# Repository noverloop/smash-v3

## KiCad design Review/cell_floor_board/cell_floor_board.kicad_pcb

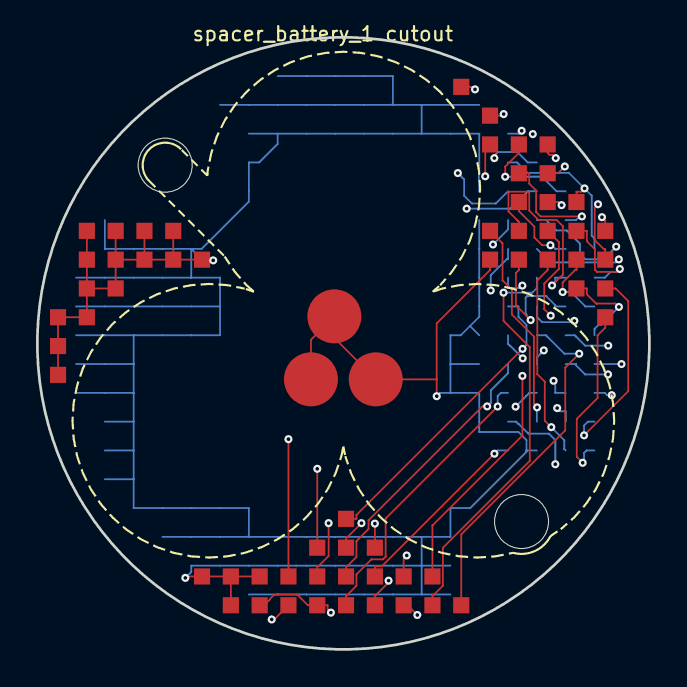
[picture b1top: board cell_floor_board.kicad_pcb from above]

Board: 6 copper layers, 34.0 x 34.0 mm, 7 parts (1 on the bottom side), 35 nets.

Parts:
J_cell_floor_board_spacer_battery_1: LGA_lands; J_cell_floor_board_spacer_battery_1
MECH1, MECH2: smash_mech_potting
P_CELL_TAB_NEG1, P_CELL_TAB_NEG2, P_CELL_TAB_NEG3: CellSolderTab; CellSolderTab_placeholder
P_cell_floor_board_spacer_activation_interface_cell_floor_board: LGA_lands; P_cell_floor_board_spacer_activation_interface_cell_floor_b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

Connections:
3V3: J_cell_floor_board_spacer_battery_1.1, J_cell_floor_board_spacer_battery_1.36, J_cell_floor_board_spacer_battery_1.41, P_cell_floor_board_spacer_activation_in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.1, P_cell_floor_board_spacer_activation_in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.36, P_cell_floor_board_spacer_activation_in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.41
3V3_AON: J_cell_floor_board_spacer_battery_1.2, J_cell_floor_board_spacer_battery_1.37, P_cell_floor_board_spacer_activation_in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.2, P_cell_floor_board_spacer_activation_in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.37
ACTIVATE_CONFIRM: J_cell_floor_board_spacer_battery_1.3, P_cell_floor_board_spacer_activation_in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.3
ACTIVATE_SET: J_cell_floor_board_spacer_battery_1.4, P_cell_floor_board_spacer_activation_in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.4
BAT_PROT: J_cell_floor_board_spacer_battery_1.5, J_cell_floor_board_spacer_battery_1.38, P_cell_floor_board_spacer_activation_in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.5, P_cell_floor_board_spacer_activation_in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.38
BAT_RAW: J_cell_floor_board_spacer_battery_1.6, J_cell_floor_board_spacer_battery_1.39, P_cell_floor_board_spacer_activation_in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.6, P_cell_floor_board_spacer_activation_in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.39
BOOT0: J_cell_floor_board_spacer_battery_1.7, P_cell_floor_board_spacer_activation_in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.7
COMP_5V: J_cell_floor_board_spacer_battery_1.8, J_cell_floor_board_spacer_battery_1.40, P_cell_floor_board_spacer_activation_in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.8, P_cell_floor_board_spacer_activation_in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.40
COMP_SWDCLK: J_cell_floor_board_spacer_battery_1.9, P_cell_floor_board_spacer_activation_in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.9
COMP_SWDIO: J_cell_floor_board_spacer_battery_1.10, P_cell_floor_board_spacer_activation_in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.10
EXT_CAN_RX: J_cell_floor_board_spacer_battery_1.11, P_cell_floor_board_spacer_activation_in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.11
EXT_CAN_TX: J_cell_floor_board_spacer_battery_1.12, P_cell_floor_board_spacer_activation_in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.12
FIN1_AOUT1: J_cell_floor_board_spacer_battery_1.13, P_cell_floor_board_spacer_activation_in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.13
FIN2_AOUT1: J_cell_floor_board_spacer_battery_1.14, P_cell_floor_board_spacer_activation_in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.14
FIN3_AOUT1: J_cell_floor_board_spacer_battery_1.15, P_cell_floor_board_spacer_activation_in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.15
FIN4_AOUT1: J_cell_floor_board_spacer_battery_1.16, P_cell_floor_board_spacer_activation_in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.16
FIN_HALL: J_cell_floor_board_spacer_battery_1.17, P_cell_floor_board_spacer_activation_in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.17
FIN_VREF: J_cell_floor_board_spacer_battery_1.18, P_cell_floor_board_spacer_activation_in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.18
FLEX_GND: J_cell_floor_board_spacer_battery_1.19, J_cell_floor_board_spacer_battery_1.42, J_cell_floor_board_spacer_battery_1.43, J_cell_floor_board_spacer_battery_1.44, J_cell_floor_board_spacer_battery_1.45, J_cell_floor_board_spacer_battery_1.46, J_cell_floor_board_spacer_battery_1.47, J_cell_floor_board_spacer_battery_1.48, J_cell_floor_board_spacer_battery_1.49, J_cell_floor_board_spacer_battery_1.50, J_cell_floor_board_spacer_battery_1.51, J_cell_floor_board_spacer_battery_1.52, J_cell_floor_board_spacer_battery_1.53, J_cell_floor_board_spacer_battery_1.54, J_cell_floor_board_spacer_battery_1.55, J_cell_floor_board_spacer_battery_1.56, J_cell_floor_board_spacer_battery_1.57, J_cell_floor_board_spacer_battery_1.58, J_cell_floor_board_spacer_battery_1.59, J_cell_floor_board_spacer_battery_1.60, P_CELL_TAB_NEG1.1, P_CELL_TAB_NEG2.1, P_CELL_TAB_NEG3.1, P_cell_floor_board_spacer_activation_in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.19, P_cell_floor_board_spacer_activation_in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.42, P_cell_floor_board_spacer_activation_in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.43, P_cell_floor_board_spacer_activation_in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.44, P_cell_floor_board_spacer_activation_in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.45, P_cell_floor_board_spacer_activation_in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.46, P_cell_floor_board_spacer_activation_in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.47, P_cell_floor_board_spacer_activation_in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.48, P_cell_floor_board_spacer_activation_in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.49, P_cell_floor_board_spacer_activation_in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.50, P_cell_floor_board_spacer_activation_in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.51, P_cell_floor_board_spacer_activation_in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.52, P_cell_floor_board_spacer_activation_in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.53, P_cell_floor_board_spacer_activation_in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.54, P_cell_floor_board_spacer_activation_in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.55, P_cell_floor_board_spacer_activation_in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.56, P_cell_floor_board_spacer_activation_in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.57, P_cell_floor_board_spacer_activation_in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.58, P_cell_floor_board_spacer_activation_in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.59, P_cell_floor_board_spacer_activation_in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.60, P_cell_floor_board_spacer_activation_in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.61, P_cell_floor_board_spacer_activation_in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.62, P_cell_floor_board_spacer_activation_in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.63, P_cell_floor_board_spacer_activation_in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.64, P_cell_floor_board_spacer_activation_in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.65, P_cell_floor_board_spacer_activation_in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.66, P_cell_floor_board_spacer_activation_in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.67, P_cell_floor_board_spacer_activation_in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.68, P_cell_floor_board_spacer_activation_in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.69, P_cell_floor_board_spacer_activation_in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.70, P_cell_floor_board_spacer_activation_in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.71, P_cell_floor_board_spacer_activation_in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.72, P_cell_floor_board_spacer_activation_in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.73, P_cell_floor_board_spacer_activation_in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.74, P_cell_floor_board_spacer_activation_in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.75, P_cell_floor_board_spacer_activation_in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.76, P_cell_floor_board_spacer_activation_in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.77, P_cell_floor_board_spacer_activation_in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.78, P_cell_floor_board_spacer_activation_in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.79, P_cell_floor_board_spacer_activation_in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.80, P_cell_floor_board_spacer_activation_in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.81, P_cell_floor_board_spacer_activation_in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.82, P_cell_floor_board_spacer_activation_in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.83, P_cell_floor_board_spacer_activation_in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.84, P_cell_floor_board_spacer_activation_in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.85, P_cell_floor_board_spacer_activation_in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.86, P_cell_floor_board_spacer_activation_in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.87, P_cell_floor_board_spacer_activation_in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.88, P_cell_floor_board_spacer_activation_in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.89, P_cell_floor_board_spacer_activation_in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.90, P_cell_floor_board_spacer_activation_in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.91, P_cell_floor_board_spacer_activation_in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.92, P_cell_floor_board_spacer_activation_in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.93, P_cell_floor_board_spacer_activation_in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.94, P_cell_floor_board_spacer_activation_in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.95, P_cell_floor_board_spacer_activation_in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.96, P_cell_floor_board_spacer_activation_in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.97, P_cell_floor_board_spacer_activation_in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.98, P_cell_floor_board_spacer_activation_in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.99, P_cell_floor_board_spacer_activation_in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.100, P_cell_floor_board_spacer_activation_in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.101, P_cell_floor_board_spacer_activation_in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.102, P_cell_floor_board_spacer_activation_in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.103, P_cell_floor_board_spacer_activation_in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.104, P_cell_floor_board_spacer_activation_in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.105, P_cell_floor_board_spacer_activation_in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.106, P_cell_floor_board_spacer_activation_in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.107, P_cell_floor_board_spacer_activation_in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.108, P_cell_floor_board_spacer_activation_in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.109, P_cell_floor_board_spacer_activation_in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.110, P_cell_floor_board_spacer_activation_in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.111, P_cell_floor_board_spacer_activation_in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.112, P_cell_floor_board_spacer_activation_in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.113, P_cell_floor_board_spacer_activation_in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.114, P_cell_floor_board_spacer_activation_in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.115, P_cell_floor_board_spacer_activation_in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.116, P_cell_floor_board_spacer_activation_in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.117, P_cell_floor_board_spacer_activation_in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.118, P_cell_floor_board_spacer_activation_in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.119, P_cell_floor_board_spacer_activation_in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.120, P_cell_floor_board_spacer_activation_in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.121, P_cell_floor_board_spacer_activation_in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.122, P_cell_floor_board_spacer_activation_in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.123, P_cell_floor_board_spacer_activation_in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.124, P_cell_floor_board_spacer_activation_in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.125, P_cell_floor_board_spacer_activation_in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.126, P_cell_floor_board_spacer_activation_in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.127, P_cell_floor_board_spacer_activation_in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.128, P_cell_floor_board_spacer_activation_in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.129, P_cell_floor_board_spacer_activation_in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.130, P_cell_floor_board_spacer_activation_in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.131, P_cell_floor_board_spacer_activation_in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.132, P_cell_floor_board_spacer_activation_in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.133, P_cell_floor_board_spacer_activation_in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.134, P_cell_floor_board_spacer_activation_in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.135, P_cell_floor_board_spacer_activation_in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.136, P_cell_floor_board_spacer_activation_in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.137, P_cell_floor_board_spacer_activation_in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.138, P_cell_floor_board_spacer_activation_in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.139, P_cell_floor_board_spacer_activation_in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.140, P_cell_floor_board_spacer_activation_in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.141, P_cell_floor_board_spacer_activation_in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.142, P_cell_floor_board_spacer_activation_in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.143, P_cell_floor_board_spacer_activation_in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.144, P_cell_floor_board_spacer_activation_in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.145, P_cell_floor_board_spacer_activation_in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.146, P_cell_floor_board_spacer_activation_in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.147, P_cell_floor_board_spacer_activation_in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.148, P_cell_floor_board_spacer_activation_in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.149, P_cell_floor_board_spacer_activation_in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.150
GPIO_EXT_0: J_cell_floor_board_spacer_battery_1.20, P_cell_floor_board_spacer_activation_in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.20
GPIO_EXT_1: J_cell_floor_board_spacer_battery_1.21, P_cell_floor_board_spacer_activation_in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.21
GPIO_EXT_2: J_cell_floor_board_spacer_battery_1.22, P_cell_floor_board_spacer_activation_in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.22
GPIO_EXT_3: J_cell_floor_board_spacer_battery_1.23, P_cell_floor_board_spacer_activation_in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.23
H3LIS_INT1: J_cell_floor_board_spacer_battery_1.24, P_cell_floor_board_spacer_activation_in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.24
I2C3_SCL: J_cell_floor_board_spacer_battery_1.25, P_cell_floor_board_spacer_activation_in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.25
I2C3_SDA: J_cell_floor_board_spacer_battery_1.26, P_cell_floor_board_spacer_activation_in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.26
JUMP_WAKE: J_cell_floor_board_spacer_battery_1.27, P_cell_floor_board_spacer_activation_in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.27
NRST: J_cell_floor_board_spacer_battery_1.28, P_cell_floor_board_spacer_activation_in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.28
SWO: J_cell_floor_board_spacer_battery_1.29, P_cell_floor_board_spacer_activation_in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.29
SYS_I2C_SCL: J_cell_floor_board_spacer_battery_1.30, P_cell_floor_board_spacer_activation_in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.30
SYS_I2C_SDA: J_cell_floor_board_spacer_battery_1.31, P_cell_floor_board_spacer_activation_in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.31
SYS_SPI_CS_FIN: J_cell_floor_board_spacer_battery_1.32, P_cell_floor_board_spacer_activation_in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.32
SYS_SPI_MISO: J_cell_floor_board_spacer_battery_1.33, P_cell_floor_board_spacer_activation_in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.33
SYS_SPI_MOSI: J_cell_floor_board_spacer_battery_1.34, P_cell_floor_board_spacer_activation_in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.34
SYS_SPI_SCLK: J_cell_floor_board_spacer_battery_1.35, P_cell_floor_board_spacer_activation_in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.35

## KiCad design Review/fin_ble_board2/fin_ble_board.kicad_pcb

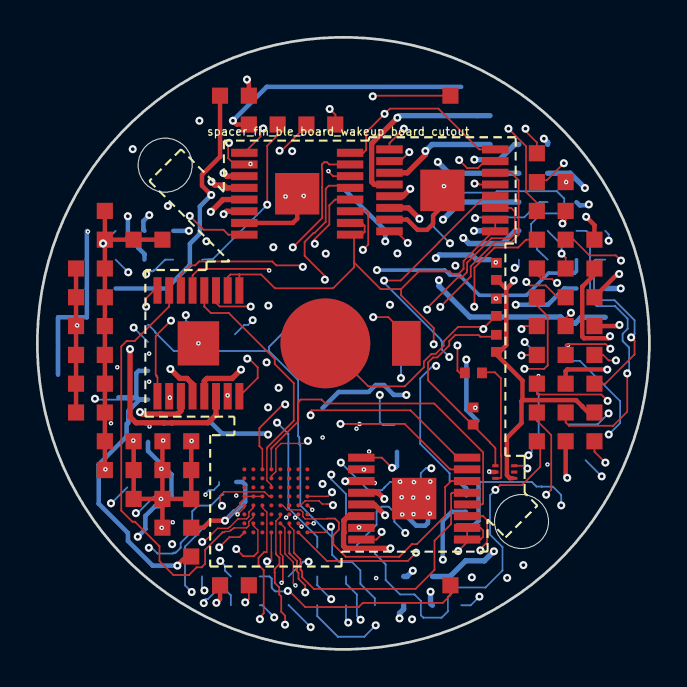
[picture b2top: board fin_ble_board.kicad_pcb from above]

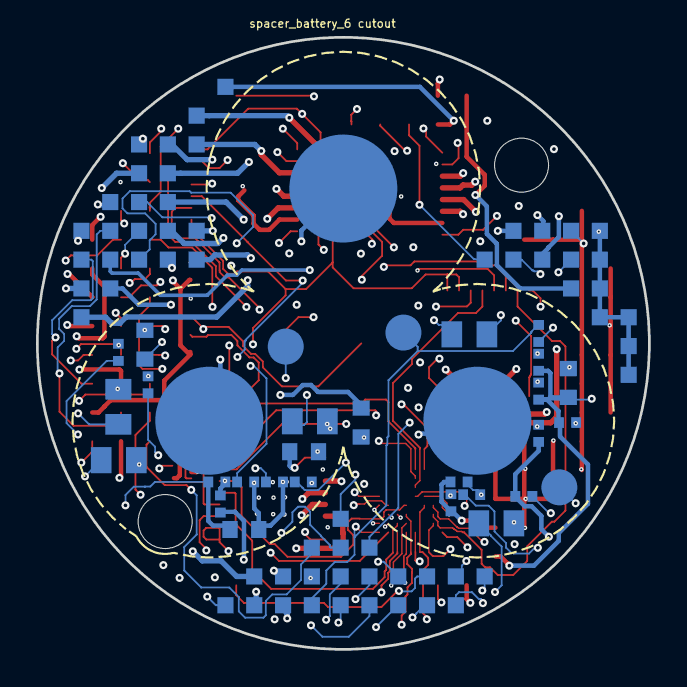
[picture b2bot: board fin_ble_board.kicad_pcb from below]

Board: 14 copper layers, 34.0 x 34.0 mm, 44 parts (31 on the bottom side), 81 nets.

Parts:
C_COMP_PZ: C0402 X7R 100nF; Capacitor_SMD_C_0402_1005Metric
C_FIN1_DVDD, C_FIN2_DVDD, C_FIN3_DVDD, C_FIN4_DVDD: C-Series MIL-PRF-32535 X7R 0805 1uF; Capacitor_SMD_C_0805_2012Metric
C_FIN1_VM, C_FIN2_VM, C_FIN3_VM, C_FIN4_VM: C0402 X7R 100nF; Capacitor_SMD_C_0402_1005Metric
C_FIN_VM_BULK_1, C_FIN_VM_BULK_2, C_FIN_VM_BULK_3, C_FIN_VM_BULK_4, C_FIN_VM_BULK_5: C-Series MIL-PRF-32535 X7R 0603 2.2uF; Capacitor_SMD_C_0603_1608Metric
C_FIN_VREF: C0402 X7R 100nF; Capacitor_SMD_C_0402_1005Metric
C_G0B1_FIN_BULK: C-Series MIL-PRF-32535 X7R 0805 1uF; Capacitor_SMD_C_0805_2012Metric
C_G0B1_FIN_NRST, C_G0B1_FIN_VDD1, C_G0B1_FIN_VDD2, C_G0B1_FIN_VREF: C0402 X7R 100nF; Capacitor_SMD_C_0402_1005Metric
C_J_HALL_FIN_VCC: C0402 X7R 100nF; Capacitor_SMD_C_0402_1005Metric
J_HALL_FIN_GND: J_HALL_FIN_GND; Pogo_Pad_D2.0mm
J_HALL_FIN_OUT: J_HALL_FIN_OUT; Pogo_Pad_D2.0mm
J_HALL_FIN_VCC: J_HALL_FIN_VCC; Pogo_Pad_D2.0mm
J_fin_ble_board_spacer_fin_ble_board_wakeup_board: LGA_lands; J_fin_ble_board_spacer_fin_ble_board_wakeup_board
P_CELL_CONTACTS: BatteryContacts_3
P_PIEZO: SMD10T04R111; PiezoDisc_SMD10T04R111
P_fin_ble_board_spacer_battery_6: LGA_lands; P_fin_ble_board_spacer_battery_6
R_COMP_SER: CRCW0402 100k 1% e3; Resistor_SMD_R_0402_1005Metric
R_FIN1_DECAY, R_FIN2_DECAY, R_FIN3_DECAY, R_FIN4_DECAY: CRCW0402 44.2k 1% e3; Resistor_SMD_R_0402_1005Metric
R_G0B1_FIN_NRST: CRCW0402 10k 1% e3; Resistor_SMD_R_0402_1005Metric
R_J_HALL_FIN_PU: CRCW0402 10k 1% e3; Resistor_SMD_R_0402_1005Metric
R_PIEZO_BLEED: CRCW0402 1M 1% e3; Resistor_SMD_R_0402_1005Metric
R_THR1: CRCW0402 1M 1% e3; Resistor_SMD_R_0402_1005Metric
R_THR2: CRCW0402 100k 1% e3; Resistor_SMD_R_0402_1005Metric
U_COMP_PZ: TLV3691IDPFR; DPF0006A
U_FIN1, U_FIN2, U_FIN3, U_FIN4: DRV8428EPWPR; SOP65P640X120-17N
U_G0B1_FIN: STM32G0B1REI6N; BGA64C50P8X8_500X500X60

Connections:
3V3: C_G0B1_FIN_BULK.1, C_G0B1_FIN_VDD1.1, C_G0B1_FIN_VDD2.1, C_G0B1_FIN_VREF.1, C_J_HALL_FIN_VCC.1, J_HALL_FIN_VCC.1, J_fin_ble_board_spacer_fin_ble_board_wa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.1, J_fin_ble_board_spacer_fin_ble_board_wa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.35, J_fin_ble_board_spacer_fin_ble_board_wa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.41, P_fin_ble_board_spacer_battery_6.23, P_fin_ble_board_spacer_battery_6.47, P_fin_ble_board_spacer_battery_6.52, R_G0B1_FIN_NRST.1, R_J_HALL_FIN_PU.1, U_G0B1_FIN.D1, U_G0B1_FIN.D2, U_G0B1_FIN.D3, U_G0B1_FIN.D8
3V3_AON: C_COMP_PZ.1, J_fin_ble_board_spacer_fin_ble_board_wa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.2, J_fin_ble_board_spacer_fin_ble_board_wa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.36, P_fin_ble_board_spacer_battery_6.24, P_fin_ble_board_spacer_battery_6.48, R_THR1.1, U_COMP_PZ.6
ACTIVATE_CONFIRM: J_fin_ble_board_spacer_fin_ble_board_wa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.3, P_fin_ble_board_spacer_battery_6.3
ACTIVATE_SET: J_fin_ble_board_spacer_fin_ble_board_wa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.4, P_fin_ble_board_spacer_battery_6.4
BAT_CELL1_POS: J_fin_ble_board_spacer_fin_ble_board_wa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.5, P_CELL_CONTACTS.1
BAT_CELL2_POS: J_fin_ble_board_spacer_fin_ble_board_wa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.6, P_CELL_CONTACTS.2
BAT_CELL3_POS: J_fin_ble_board_spacer_fin_ble_board_wa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.7, P_CELL_CONTACTS.3
BAT_PROT: J_fin_ble_board_spacer_fin_ble_board_wa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.8, J_fin_ble_board_spacer_fin_ble_board_wa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.37, P_fin_ble_board_spacer_battery_6.5, P_fin_ble_board_spacer_battery_6.49
BAT_RAW: J_fin_ble_board_spacer_fin_ble_board_wa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.9, J_fin_ble_board_spacer_fin_ble_board_wa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.38, P_fin_ble_board_spacer_battery_6.6, P_fin_ble_board_spacer_battery_6.50
BOOT0: J_fin_ble_board_spacer_fin_ble_board_wa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.10, P_fin_ble_board_spacer_battery_6.7
COMP_5V: J_fin_ble_board_spacer_fin_ble_board_wa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.11, J_fin_ble_board_spacer_fin_ble_board_wa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.39, P_fin_ble_board_spacer_battery_6.8, P_fin_ble_board_spacer_battery_6.51
COMP_5V_RAW: C_FIN1_VM.1, C_FIN2_VM.1, C_FIN3_VM.1, C_FIN4_VM.1, C_FIN_VM_BULK_1.1, C_FIN_VM_BULK_2.1, C_FIN_VM_BULK_3.1, C_FIN_VM_BULK_4.1, C_FIN_VM_BULK_5.1, J_fin_ble_board_spacer_fin_ble_board_wa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.12, J_fin_ble_board_spacer_fin_ble_board_wa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.40, U_FIN1.1, U_FIN2.1, U_FIN3.1, U_FIN4.1
COMP_INM: R_THR1.2, R_THR2.1, U_COMP_PZ.3
COMP_INP: R_COMP_SER.2, U_COMP_PZ.1
COMP_OUT: J_fin_ble_board_spacer_fin_ble_board_wa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.13, U_COMP_PZ.4
COMP_SWDCLK: J_fin_ble_board_spacer_fin_ble_board_wa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.14, P_fin_ble_board_spacer_battery_6.9
COMP_SWDIO: J_fin_ble_board_spacer_fin_ble_board_wa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.15, P_fin_ble_board_spacer_battery_6.10
EXT_CAN_RX: J_fin_ble_board_spacer_fin_ble_board_wa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.16, P_fin_ble_board_spacer_battery_6.11
EXT_CAN_TX: J_fin_ble_board_spacer_fin_ble_board_wa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.17, P_fin_ble_board_spacer_battery_6.14
FIN1_AEN: U_FIN1.15, U_G0B1_FIN.E3
FIN1_AOUT1: P_fin_ble_board_spacer_battery_6.13, U_FIN1.3
FIN1_AOUT2: P_fin_ble_board_spacer_battery_6.12, U_FIN1.4
FIN1_APH: U_FIN1.14, U_G0B1_FIN.H5
FIN1_BEN: U_FIN1.13, U_G0B1_FIN.F5
FIN1_BOUT1: P_fin_ble_board_spacer_battery_6.15, U_FIN1.6
FIN1_BOUT2: P_fin_ble_board_spacer_battery_6.16, U_FIN1.5
FIN1_BPH: U_FIN1.12, U_G0B1_FIN.B4
FIN1_DECAY: R_FIN1_DECAY.1, U_FIN1.11
FIN1_DVDD: C_FIN1_DVDD.1, U_FIN1.8
FIN2_AEN: U_FIN2.15, U_G0B1_FIN.F2
FIN2_AOUT1: P_fin_ble_board_spacer_battery_6.17, U_FIN2.3
FIN2_AOUT2: P_fin_ble_board_spacer_battery_6.18, U_FIN2.4
FIN2_APH: U_FIN2.14, U_G0B1_FIN.H6
FIN2_BEN: U_FIN2.13, U_G0B1_FIN.G5
FIN2_BOUT1: P_fin_ble_board_spacer_battery_6.19, U_FIN2.6
FIN2_BOUT2: P_fin_ble_board_spacer_battery_6.20, U_FIN2.5
FIN2_BPH: U_FIN2.12, U_G0B1_FIN.C4
FIN2_DECAY: R_FIN2_DECAY.1, U_FIN2.11
FIN2_DVDD: C_FIN2_DVDD.1, U_FIN2.8
FIN3_AEN: U_FIN3.15, U_G0B1_FIN.G2
FIN3_AOUT1: P_fin_ble_board_spacer_battery_6.21, U_FIN3.3
FIN3_AOUT2: P_fin_ble_board_spacer_battery_6.22, U_FIN3.4
FIN3_APH: U_FIN3.14, U_G0B1_FIN.E7
FIN3_BEN: U_FIN3.13, U_G0B1_FIN.H7
FIN3_BOUT1: P_fin_ble_board_spacer_battery_6.1, U_FIN3.6
FIN3_BOUT2: P_fin_ble_board_spacer_battery_6.2, U_FIN3.5
FIN3_BPH: U_FIN3.12, U_G0B1_FIN.D4
FIN3_DECAY: R_FIN3_DECAY.1, U_FIN3.11
FIN3_DVDD: C_FIN3_DVDD.1, U_FIN3.8
FIN4_AEN: U_FIN4.15, U_G0B1_FIN.H1
FIN4_AOUT1: P_fin_ble_board_spacer_battery_6.25, U_FIN4.3
FIN4_AOUT2: P_fin_ble_board_spacer_battery_6.26, U_FIN4.4
FIN4_APH: U_FIN4.14, U_G0B1_FIN.E5
FIN4_BEN: U_FIN4.13, U_G0B1_FIN.G6
FIN4_BOUT1: P_fin_ble_board_spacer_battery_6.27, U_FIN4.6
FIN4_BOUT2: P_fin_ble_board_spacer_battery_6.28, U_FIN4.5
FIN4_BPH: U_FIN4.12, U_G0B1_FIN.A4
FIN4_DECAY: R_FIN4_DECAY.1, U_FIN4.11
FIN4_DVDD: C_FIN4_DVDD.1, U_FIN4.8
FIN_HALL: J_HALL_FIN_OUT.1, P_fin_ble_board_spacer_battery_6.29, R_J_HALL_FIN_PU.2, U_G0B1_FIN.H8
FIN_NSLEEP: U_FIN1.16, U_FIN2.16, U_FIN3.16, U_FIN4.16, U_G0B1_FIN.A3
FIN_VREF: C_FIN_VREF.1, U_FIN1.9, U_FIN1.10, U_FIN2.9, U_FIN2.10, U_FIN3.9, U_FIN3.10, U_FIN4.9, U_FIN4.10, U_G0B1_FIN.H4
FLEX_GND: C_COMP_PZ.2, C_FIN1_DVDD.2, C_FIN1_VM.2, C_FIN2_DVDD.2, C_FIN2_VM.2, C_FIN3_DVDD.2, C_FIN3_VM.2, C_FIN4_DVDD.2, C_FIN4_VM.2, C_FIN_VM_BULK_1.2, C_FIN_VM_BULK_2.2, C_FIN_VM_BULK_3.2, C_FIN_VM_BULK_4.2, C_FIN_VM_BULK_5.2, C_FIN_VREF.2, C_G0B1_FIN_BULK.2, C_G0B1_FIN_NRST.2, C_G0B1_FIN_VDD1.2, C_G0B1_FIN_VDD2.2, C_G0B1_FIN_VREF.2, C_J_HALL_FIN_VCC.2, J_HALL_FIN_GND.1, J_fin_ble_board_spacer_fin_ble_board_wa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.18, J_fin_ble_board_spacer_fin_ble_board_wa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.42, J_fin_ble_board_spacer_fin_ble_board_wa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.43, J_fin_ble_board_spacer_fin_ble_board_wa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.44, J_fin_ble_board_spacer_fin_ble_board_wa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.45, J_fin_ble_board_spacer_fin_ble_board_wa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.46, J_fin_ble_board_spacer_fin_ble_board_wa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.47, J_fin_ble_board_spacer_fin_ble_board_wa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.48, J_fin_ble_board_spacer_fin_ble_board_wa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.49, J_fin_ble_board_spacer_fin_ble_board_wa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.50, J_fin_ble_board_spacer_fin_ble_board_wa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.51, J_fin_ble_board_spacer_fin_ble_board_wa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.52, J_fin_ble_board_spacer_fin_ble_board_wa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.53, J_fin_ble_board_spacer_fin_ble_board_wa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.54, J_fin_ble_board_spacer_fin_ble_board_wa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.55, J_fin_ble_board_spacer_fin_ble_board_wa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.56, J_fin_ble_board_spacer_fin_ble_board_wa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.57, J_fin_ble_board_spacer_fin_ble_board_wa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.58, J_fin_ble_board_spacer_fin_ble_board_wa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.59, J_fin_ble_board_spacer_fin_ble_board_wa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.60, J_fin_ble_board_spacer_fin_ble_board_wa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.61, J_fin_ble_board_spacer_fin_ble_board_wa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.62, J_fin_ble_board_spacer_fin_ble_board_wa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.63, J_fin_ble_board_spacer_fin_ble_board_wa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.64, J_fin_ble_board_spacer_fin_ble_board_wa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.65, J_fin_ble_board_spacer_fin_ble_board_wa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.66, J_fin_ble_board_spacer_fin_ble_board_wa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.67, J_fin_ble_board_spacer_fin_ble_board_wa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.68, J_fin_ble_board_spacer_fin_ble_board_wa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.69, P_PIEZO.2, P_fin_ble_board_spacer_battery_6.30, P_fin_ble_board_spacer_battery_6.53, P_fin_ble_board_spacer_battery_6.54, P_fin_ble_board_spacer_battery_6.55, P_fin_ble_board_spacer_battery_6.56, P_fin_ble_board_spacer_battery_6.57, P_fin_ble_board_spacer_battery_6.58, P_fin_ble_board_spacer_battery_6.59, P_fin_ble_board_spacer_battery_6.60, R_FIN1_DECAY.2, R_FIN2_DECAY.2, R_FIN3_DECAY.2, R_FIN4_DECAY.2, R_PIEZO_BLEED.2, R_THR2.2, U_COMP_PZ.2, U_FIN1.2, U_FIN1.7, U_FIN1.17, U_FIN2.2, U_FIN2.7, U_FIN2.17, U_FIN3.2, U_FIN3.7, U_FIN3.17, U_FIN4.2, U_FIN4.7, U_FIN4.17, U_G0B1_FIN.E1, U_G0B1_FIN.E8
G0B1_FIN_NRST: C_G0B1_FIN_NRST.1, R_G0B1_FIN_NRST.2, U_G0B1_FIN.E2
GPIO_EXT_0: J_fin_ble_board_spacer_fin_ble_board_wa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.19, P_fin_ble_board_spacer_battery_6.31
GPIO_EXT_1: J_fin_ble_board_spacer_fin_ble_board_wa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.20, P_fin_ble_board_spacer_battery_6.32
GPIO_EXT_2: J_fin_ble_board_spacer_fin_ble_board_wa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.21, P_fin_ble_board_spacer_battery_6.33
GPIO_EXT_3: J_fin_ble_board_spacer_fin_ble_board_wa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.22, P_fin_ble_board_spacer_battery_6.34
H3LIS_INT1: J_fin_ble_board_spacer_fin_ble_board_wa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.23, P_fin_ble_board_spacer_battery_6.35
I2C3_SCL: J_fin_ble_board_spacer_fin_ble_board_wa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.24, P_fin_ble_board_spacer_battery_6.36
I2C3_SDA: J_fin_ble_board_spacer_fin_ble_board_wa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.25, P_fin_ble_board_spacer_battery_6.37
JUMP_WAKE: J_fin_ble_board_spacer_fin_ble_board_wa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.26, P_fin_ble_board_spacer_battery_6.38
NRST: J_fin_ble_board_spacer_fin_ble_board_wa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.27, P_fin_ble_board_spacer_battery_6.39
PIEZO_P: P_PIEZO.1, R_COMP_SER.1, R_PIEZO_BLEED.1
SWO: J_fin_ble_board_spacer_fin_ble_board_wa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.28, P_fin_ble_board_spacer_battery_6.40
SYS_I2C_SCL: J_fin_ble_board_spacer_fin_ble_board_wa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.29, P_fin_ble_board_spacer_battery_6.41
SYS_I2C_SDA: J_fin_ble_board_spacer_fin_ble_board_wa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.30, P_fin_ble_board_spacer_battery_6.42
SYS_SPI_CS_FIN: J_fin_ble_board_spacer_fin_ble_board_wa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.31, P_fin_ble_board_spacer_battery_6.43, U_G0B1_FIN.G7
SYS_SPI_MISO: J_fin_ble_board_spacer_fin_ble_board_wa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.32, P_fin_ble_board_spacer_battery_6.44, U_G0B1_FIN.F6
SYS_SPI_MOSI: J_fin_ble_board_spacer_fin_ble_board_wa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.33, P_fin_ble_board_spacer_battery_6.45, U_G0B1_FIN.F7
SYS_SPI_SCLK: J_fin_ble_board_spacer_fin_ble_board_wa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.34, P_fin_ble_board_spacer_battery_6.46, U_G0B1_FIN.G8

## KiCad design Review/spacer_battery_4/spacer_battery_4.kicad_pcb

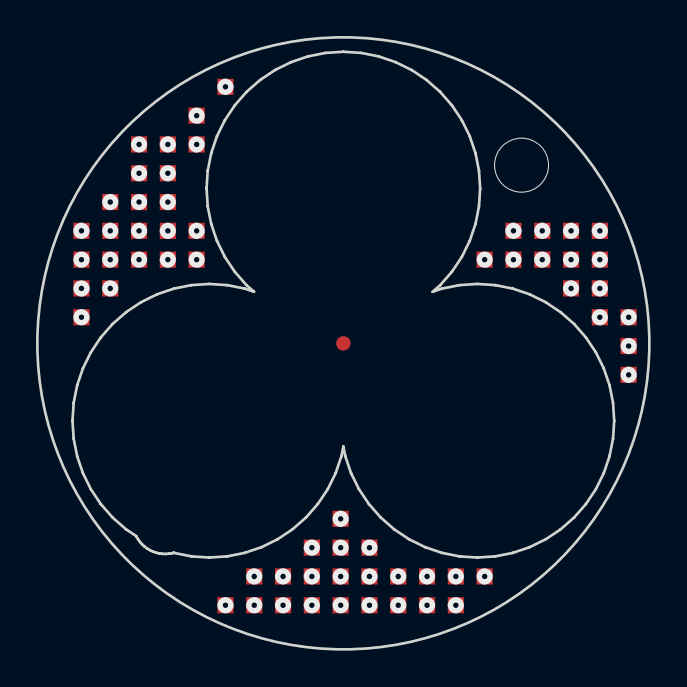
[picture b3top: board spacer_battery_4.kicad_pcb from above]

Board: 2 copper layers, 34.0 x 34.0 mm, 3 parts (1 on the bottom side), 35 nets, no tracks yet.

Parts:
J_spacer_battery_4_top: LGA_lands; J_spacer_battery_4_top
P_spacer_battery_4_bot: LGA_lands; P_spacer_battery_4_bot
SP_battery_4: SP_battery_4; Spacer_Mechanical_34mm

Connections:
3V3: J_spacer_battery_4_top.1, J_spacer_battery_4_top.36, J_spacer_battery_4_top.41, P_spacer_battery_4_bot.1, P_spacer_battery_4_bot.36, P_spacer_battery_4_bot.41
3V3_AON: J_spacer_battery_4_top.2, J_spacer_battery_4_top.37, P_spacer_battery_4_bot.2, P_spacer_battery_4_bot.37
ACTIVATE_CONFIRM: J_spacer_battery_4_top.3, P_spacer_battery_4_bot.3
ACTIVATE_SET: J_spacer_battery_4_top.4, P_spacer_battery_4_bot.4
BAT_PROT: J_spacer_battery_4_top.5, J_spacer_battery_4_top.38, P_spacer_battery_4_bot.5, P_spacer_battery_4_bot.38
BAT_RAW: J_spacer_battery_4_top.6, J_spacer_battery_4_top.39, P_spacer_battery_4_bot.6, P_spacer_battery_4_bot.39
BOOT0: J_spacer_battery_4_top.7, P_spacer_battery_4_bot.7
COMP_5V: J_spacer_battery_4_top.8, J_spacer_battery_4_top.40, P_spacer_battery_4_bot.8, P_spacer_battery_4_bot.40
COMP_SWDCLK: J_spacer_battery_4_top.9, P_spacer_battery_4_bot.9
COMP_SWDIO: J_spacer_battery_4_top.10, P_spacer_battery_4_bot.10
EXT_CAN_RX: J_spacer_battery_4_top.11, P_spacer_battery_4_bot.11
EXT_CAN_TX: J_spacer_battery_4_top.12, P_spacer_battery_4_bot.12
FIN1_AOUT1: J_spacer_battery_4_top.13, P_spacer_battery_4_bot.13
FIN2_AOUT1: J_spacer_battery_4_top.14, P_spacer_battery_4_bot.14
FIN3_AOUT1: J_spacer_battery_4_top.15, P_spacer_battery_4_bot.15
FIN4_AOUT1: J_spacer_battery_4_top.16, P_spacer_battery_4_bot.16
FIN_HALL: J_spacer_battery_4_top.17, P_spacer_battery_4_bot.17
FIN_VREF: J_spacer_battery_4_top.18, P_spacer_battery_4_bot.18
FLEX_GND: J_spacer_battery_4_top.19, J_spacer_battery_4_top.42, J_spacer_battery_4_top.43, J_spacer_battery_4_top.44, J_spacer_battery_4_top.45, J_spacer_battery_4_top.46, J_spacer_battery_4_top.47, J_spacer_battery_4_top.48, J_spacer_battery_4_top.49, J_spacer_battery_4_top.50, J_spacer_battery_4_top.51, J_spacer_battery_4_top.52, J_spacer_battery_4_top.53, J_spacer_battery_4_top.54, J_spacer_battery_4_top.55, J_spacer_battery_4_top.56, J_spacer_battery_4_top.57, J_spacer_battery_4_top.58, J_spacer_battery_4_top.59, J_spacer_battery_4_top.60, P_spacer_battery_4_bot.19, P_spacer_battery_4_bot.42, P_spacer_battery_4_bot.43, P_spacer_battery_4_bot.44, P_spacer_battery_4_bot.45, P_spacer_battery_4_bot.46, P_spacer_battery_4_bot.47, P_spacer_battery_4_bot.48, P_spacer_battery_4_bot.49, P_spacer_battery_4_bot.50, P_spacer_battery_4_bot.51, P_spacer_battery_4_bot.52, P_spacer_battery_4_bot.53, P_spacer_battery_4_bot.54, P_spacer_battery_4_bot.55, P_spacer_battery_4_bot.56, P_spacer_battery_4_bot.57, P_spacer_battery_4_bot.58, P_spacer_battery_4_bot.59, P_spacer_battery_4_bot.60, SP_battery_4.1
GPIO_EXT_0: J_spacer_battery_4_top.20, P_spacer_battery_4_bot.20
GPIO_EXT_1: J_spacer_battery_4_top.21, P_spacer_battery_4_bot.21
GPIO_EXT_2: J_spacer_battery_4_top.22, P_spacer_battery_4_bot.22
GPIO_EXT_3: J_spacer_battery_4_top.23, P_spacer_battery_4_bot.23
H3LIS_INT1: J_spacer_battery_4_top.24, P_spacer_battery_4_bot.24
I2C3_SCL: J_spacer_battery_4_top.25, P_spacer_battery_4_bot.25
I2C3_SDA: J_spacer_battery_4_top.26, P_spacer_battery_4_bot.26
JUMP_WAKE: J_spacer_battery_4_top.27, P_spacer_battery_4_bot.27
NRST: J_spacer_battery_4_top.28, P_spacer_battery_4_bot.28
SWO: J_spacer_battery_4_top.29, P_spacer_battery_4_bot.29
SYS_I2C_SCL: J_spacer_battery_4_top.30, P_spacer_battery_4_bot.30
SYS_I2C_SDA: J_spacer_battery_4_top.31, P_spacer_battery_4_bot.31
SYS_SPI_CS_FIN: J_spacer_battery_4_top.32, P_spacer_battery_4_bot.32
SYS_SPI_MISO: J_spacer_battery_4_top.33, P_spacer_battery_4_bot.33
SYS_SPI_MOSI: J_spacer_battery_4_top.34, P_spacer_battery_4_bot.34
SYS_SPI_SCLK: J_spacer_battery_4_top.35, P_spacer_battery_4_bot.35

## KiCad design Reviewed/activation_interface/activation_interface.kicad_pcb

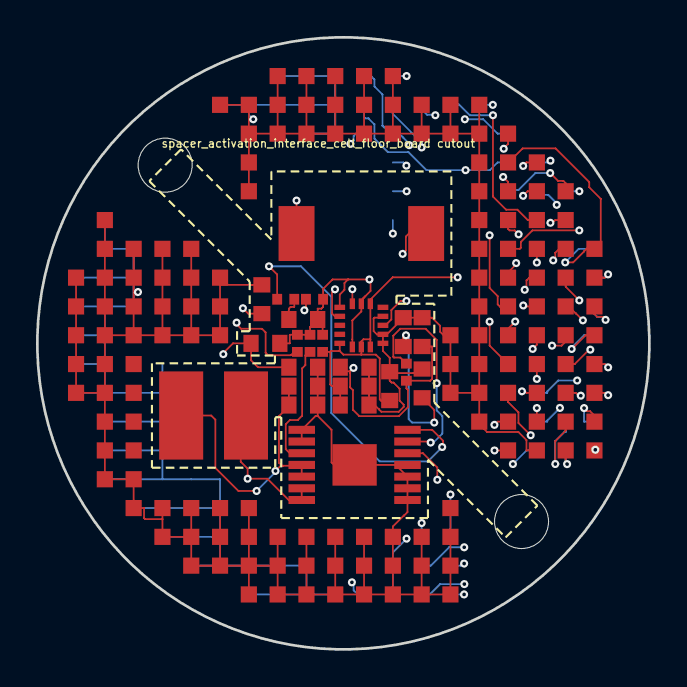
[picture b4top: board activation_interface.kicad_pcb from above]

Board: 14 copper layers, 34.0 x 34.0 mm, 25 parts (1 on the bottom side), 53 nets.

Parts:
C_ACTIVATE_COMP: C-Series MIL-PRF-32535 X7R 0603 220nF; Capacitor_SMD_C_0603_1608Metric
C_ACTIVATE_IN_1, C_ACTIVATE_IN_2, C_ACTIVATE_IN_3, C_ACTIVATE_IN_4, C_ACTIVATE_IN_5: C-Series MIL-PRF-32535 X7R 0603 2.2uF; Capacitor_SMD_C_0603_1608Metric
C_ACTIVATE_OUT_1, C_ACTIVATE_OUT_2: C-Series MIL-PRF-32535 X7R 0603 2.2uF; Capacitor_SMD_C_0603_1608Metric
C_ACTIVATE_SS: C0402 X7R 47nF; Capacitor_SMD_C_0402_1005Metric
C_HACC1: C0402 X7R 100nF; Capacitor_SMD_C_0402_1005Metric
C_HACC2_1, C_HACC2_2, C_HACC2_3, C_HACC2_4, C_HACC2_5: C-Series MIL-PRF-32535 X7R 0603 2.2uF; Capacitor_SMD_C_0603_1608Metric
D_ACTIVATE: MBRS540T3G; DIOM7958X256N
J_activation_interface_spacer_activation_interface_cell_floor_board: LGA_lands; J_activation_interface_spacer_activation_interface_cell_flo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
L_ACTIVATE: 744043100; INDPM4848X280N
P_activation_interface_spacer_aft_end_board_activation_interface: LGA_lands; P_activation_interface_spacer_aft_end_board_activation_inte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
R_ACTIVATE_COMP: CRCW0402 1.6k 1% e3; Resistor_SMD_R_0402_1005Metric
R_ACTIVATE_FB1: CRCW0402 261k 1% e3; Resistor_SMD_R_0402_1005Metric
R_ACTIVATE_FB2: CRCW0402 10k 1% e3; Resistor_SMD_R_0402_1005Metric
R_ACTIVATE_FREQ: CRCW0402 176k 1% e3; Resistor_SMD_R_0402_1005Metric
U_ACTIVATE_BOOST: TPS61175PWPR; SOP65P640X120-15N
U_HACC: H3LIS331DLTR; LIS3DHTR (LGA-16)

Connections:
3V3: C_HACC1.1, C_HACC2_1.1, C_HACC2_2.1, C_HACC2_3.1, C_HACC2_4.1, C_HACC2_5.1, J_activation_interface_spacer_activatio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.1, J_activation_interface_spacer_activatio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.47, J_activation_interface_spacer_activatio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.52, P_activation_interface_spacer_aft_end_b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.1, P_activation_interface_spacer_aft_end_b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.45, P_activation_interface_spacer_aft_end_b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.51, U_HACC.1, U_HACC.8, U_HACC.14, U_HACC.15
3V3_AON: J_activation_interface_spacer_activatio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.2, J_activation_interface_spacer_activatio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.48, P_activation_interface_spacer_aft_end_b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.2, P_activation_interface_spacer_aft_end_b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.46
ACTIVATE_COMP: R_ACTIVATE_COMP.1, U_ACTIVATE_BOOST.8
ACTIVATE_COMP_C: C_ACTIVATE_COMP.1, R_ACTIVATE_COMP.2
ACTIVATE_CONFIRM: J_activation_interface_spacer_activatio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.3, P_activation_interface_spacer_aft_end_b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.3
ACTIVATE_FB: R_ACTIVATE_FB1.2, R_ACTIVATE_FB2.1, U_ACTIVATE_BOOST.9
ACTIVATE_FREQ: R_ACTIVATE_FREQ.1, U_ACTIVATE_BOOST.10
ACTIVATE_HV: C_ACTIVATE_OUT_1.1, C_ACTIVATE_OUT_2.1, D_ACTIVATE.1, P_activation_interface_spacer_aft_end_b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.28, P_activation_interface_spacer_aft_end_b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.50, R_ACTIVATE_FB1.1
ACTIVATE_SET: J_activation_interface_spacer_activatio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.4, P_activation_interface_spacer_aft_end_b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.4
ACTIVATE_SS: C_ACTIVATE_SS.1, U_ACTIVATE_BOOST.5
ACTIVATE_SW: D_ACTIVATE.2, L_ACTIVATE.2, U_ACTIVATE_BOOST.1, U_ACTIVATE_BOOST.2
BAT_PROT: J_activation_interface_spacer_activatio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.5, J_activation_interface_spacer_activatio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.49, P_activation_interface_spacer_aft_end_b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.5, P_activation_interface_spacer_aft_end_b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.47
BAT_RAW: J_activation_interface_spacer_activatio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.6, J_activation_interface_spacer_activatio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.50, P_activation_interface_spacer_aft_end_b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.6, P_activation_interface_spacer_aft_end_b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.48
BOOT0: J_activation_interface_spacer_activatio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.7, P_activation_interface_spacer_aft_end_b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.7
COMP_5V: C_ACTIVATE_IN_1.1, C_ACTIVATE_IN_2.1, C_ACTIVATE_IN_3.1, C_ACTIVATE_IN_4.1, C_ACTIVATE_IN_5.1, J_activation_interface_spacer_activatio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.8, J_activation_interface_spacer_activatio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.51, L_ACTIVATE.1, P_activation_interface_spacer_aft_end_b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.8, P_activation_interface_spacer_aft_end_b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.49, U_ACTIVATE_BOOST.3, U_ACTIVATE_BOOST.4
COMP_SWDCLK: J_activation_interface_spacer_activatio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.9, P_activation_interface_spacer_aft_end_b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.9
COMP_SWDIO: J_activation_interface_spacer_activatio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.10, P_activation_interface_spacer_aft_end_b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.10
EXT_CAN_RX: J_activation_interface_spacer_activatio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.11, P_activation_interface_spacer_aft_end_b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.16
EXT_CAN_TX: J_activation_interface_spacer_activatio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.12, P_activation_interface_spacer_aft_end_b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.12
FIN1_AOUT1: J_activation_interface_spacer_activatio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.13, P_activation_interface_spacer_aft_end_b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.13
FIN1_AOUT2: J_activation_interface_spacer_activatio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.14, P_activation_interface_spacer_aft_end_b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.14
FIN1_BOUT1: J_activation_interface_spacer_activatio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.15, P_activation_interface_spacer_aft_end_b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.15
FIN1_BOUT2: J_activation_interface_spacer_activatio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.16, P_activation_interface_spacer_aft_end_b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.11
FIN2_AOUT1: J_activation_interface_spacer_activatio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.17, P_activation_interface_spacer_aft_end_b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.17
FIN2_AOUT2: J_activation_interface_spacer_activatio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.18, P_activation_interface_spacer_aft_end_b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.18
FIN2_BOUT1: J_activation_interface_spacer_activatio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.19, P_activation_interface_spacer_aft_end_b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.19
FIN2_BOUT2: J_activation_interface_spacer_activatio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.20, P_activation_interface_spacer_aft_end_b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.20
FIN3_AOUT1: J_activation_interface_spacer_activatio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.21, P_activation_interface_spacer_aft_end_b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.21
FIN3_AOUT2: J_activation_interface_spacer_activatio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.22, P_activation_interface_spacer_aft_end_b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.22
FIN3_BOUT1: J_activation_interface_spacer_activatio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.23, P_activation_interface_spacer_aft_end_b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.23
FIN3_BOUT2: J_activation_interface_spacer_activatio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.24, P_activation_interface_spacer_aft_end_b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.24
FIN4_AOUT1: J_activation_interface_spacer_activatio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.25, P_activation_interface_spacer_aft_end_b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.25
FIN4_AOUT2: J_activation_interface_spacer_activatio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.26, P_activation_interface_spacer_aft_end_b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.30
FIN4_BOUT1: J_activation_interface_spacer_activatio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.27, P_activation_interface_spacer_aft_end_b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.27
FIN4_BOUT2: J_activation_interface_spacer_activatio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.28, P_activation_interface_spacer_aft_end_b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.26
FIN_HALL: J_activation_interface_spacer_activatio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.29, P_activation_interface_spacer_aft_end_b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.29
FLEX_GND: C_ACTIVATE_COMP.2, C_ACTIVATE_IN_1.2, C_ACTIVATE_IN_2.2, C_ACTIVATE_IN_3.2, C_ACTIVATE_IN_4.2, C_ACTIVATE_IN_5.2, C_ACTIVATE_OUT_1.2, C_ACTIVATE_OUT_2.2, C_ACTIVATE_SS.2, C_HACC1.2, C_HACC2_1.2, C_HACC2_2.2, C_HACC2_3.2, C_HACC2_4.2, C_HACC2_5.2, J_activation_interface_spacer_activatio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.30, J_activation_interface_spacer_activatio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.53, J_activation_interface_spacer_activatio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.54, J_activation_interface_spacer_activatio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.55, J_activation_interface_spacer_activatio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.56, J_activation_interface_spacer_activatio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.57, J_activation_interface_spacer_activatio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.58, J_activation_interface_spacer_activatio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.59, J_activation_interface_spacer_activatio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.60, J_activation_interface_spacer_activatio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.61, J_activation_interface_spacer_activatio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.62, J_activation_interface_spacer_activatio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.63, J_activation_interface_spacer_activatio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.64, J_activation_interface_spacer_activatio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.65, J_activation_interface_spacer_activatio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.66, J_activation_interface_spacer_activatio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.67, J_activation_interface_spacer_activatio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.68, J_activation_interface_spacer_activatio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.69, J_activation_interface_spacer_activatio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.70, J_activation_interface_spacer_activatio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.71, J_activation_interface_spacer_activatio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.72, J_activation_interface_spacer_activatio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.73, J_activation_interface_spacer_activatio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.74, J_activation_interface_spacer_activatio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.75, J_activation_interface_spacer_activatio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.76, J_activation_interface_spacer_activatio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.77, J_activation_interface_spacer_activatio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.78, J_activation_interface_spacer_activatio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.79, J_activation_interface_spacer_activatio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.80, J_activation_interface_spacer_activatio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.81, J_activation_interface_spacer_activatio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.82, J_activation_interface_spacer_activatio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.83, J_activation_interface_spacer_activatio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.84, J_activation_interface_spacer_activatio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.85, J_activation_interface_spacer_activatio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.86, J_activation_interface_spacer_activatio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.87, J_activation_interface_spacer_activatio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.88, J_activation_interface_spacer_activatio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.89, J_activation_interface_spacer_activatio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.90, J_activation_interface_spacer_activatio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.91, J_activation_interface_spacer_activatio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.92, J_activation_interface_spacer_activatio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.93, J_activation_interface_spacer_activatio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.94, J_activation_interface_spacer_activatio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.95, J_activation_interface_spacer_activatio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.96, J_activation_interface_spacer_activatio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.97, J_activation_interface_spacer_activatio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.98, J_activation_interface_spacer_activatio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.99, J_activation_interface_spacer_activatio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.100, J_activation_interface_spacer_activatio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.101, J_activation_interface_spacer_activatio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.102, J_activation_interface_spacer_activatio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.103, J_activation_interface_spacer_activatio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.104, J_activation_interface_spacer_activatio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.105, J_activation_interface_spacer_activatio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.106, J_activation_interface_spacer_activatio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.107, J_activation_interface_spacer_activatio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.108, J_activation_interface_spacer_activatio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.109, J_activation_interface_spacer_activatio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.110, J_activation_interface_spacer_activatio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.111, J_activation_interface_spacer_activatio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.112, J_activation_interface_spacer_activatio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.113, J_activation_interface_spacer_activatio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.114, J_activation_interface_spacer_activatio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.115, J_activation_interface_spacer_activatio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.116, J_activation_interface_spacer_activatio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.117, J_activation_interface_spacer_activatio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.118, J_activation_interface_spacer_activatio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.119, J_activation_interface_spacer_activatio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.120, J_activation_interface_spacer_activatio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.121, J_activation_interface_spacer_activatio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.122, J_activation_interface_spacer_activatio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.123, J_activation_interface_spacer_activatio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.124, J_activation_interface_spacer_activatio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.125, J_activation_interface_spacer_activatio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.126, J_activation_interface_spacer_activatio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.127, J_activation_interface_spacer_activatio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.128, J_activation_interface_spacer_activatio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.129, J_activation_interface_spacer_activatio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.130, J_activation_interface_spacer_activatio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.131, J_activation_interface_spacer_activatio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.132, J_activation_interface_spacer_activatio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.133, J_activation_interface_spacer_activatio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.134, J_activation_interface_spacer_activatio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.135, J_activation_interface_spacer_activatio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.136, J_activation_interface_spacer_activatio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.137, J_activation_interface_spacer_activatio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.138, J_activation_interface_spacer_activatio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.139, J_activation_interface_spacer_activatio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.140, J_activation_interface_spacer_activatio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.141, J_activation_interface_spacer_activatio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.142, J_activation_interface_spacer_activatio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.143, J_activation_interface_spacer_activatio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.144, J_activation_interface_spacer_activatio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.145, J_activation_interface_spacer_activatio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.146, J_activation_interface_spacer_activatio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.147, J_activation_interface_spacer_activatio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.148, J_activation_interface_spacer_activatio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.149, J_activation_interface_spacer_activatio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.150, P_activation_interface_spacer_aft_end_b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.31, P_activation_interface_spacer_aft_end_b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.52, P_activation_interface_spacer_aft_end_b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.53, P_activation_interface_spacer_aft_end_b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.54, P_activation_interface_spacer_aft_end_b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.55, P_activation_interface_spacer_aft_end_b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.56, P_activation_interface_spacer_aft_end_b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.57, P_activation_interface_spacer_aft_end_b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.58, P_activation_interface_spacer_aft_end_b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.59, P_activation_interface_spacer_aft_end_b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.60, P_activation_interface_spacer_aft_end_b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.61, P_activation_interface_spacer_aft_end_b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.62, P_activation_interface_spacer_aft_end_b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.63, P_activation_interface_spacer_aft_end_b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.64, P_activation_interface_spacer_aft_end_b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.65, P_activation_interface_spacer_aft_end_b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.66, P_activation_interface_spacer_aft_end_b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.67, P_activation_interface_spacer_aft_end_b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.68, P_activation_interface_spacer_aft_end_b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.69, P_activation_interface_spacer_aft_end_b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.70, P_activation_interface_spacer_aft_end_b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.71, P_activation_interface_spacer_aft_end_b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.72, P_activation_interface_spacer_aft_end_b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.73, P_activation_interface_spacer_aft_end_b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.74, P_activation_interface_spacer_aft_end_b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.75, P_activation_interface_spacer_aft_end_b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.76, P_activation_interface_spacer_aft_end_b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.77, P_activation_interface_spacer_aft_end_b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.78, P_activation_interface_spacer_aft_end_b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.79, P_activation_interface_spacer_aft_end_b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.80, P_activation_interface_spacer_aft_end_b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.81, P_activation_interface_spacer_aft_end_b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.82, P_activation_interface_spacer_aft_end_b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.83, P_activation_interface_spacer_aft_end_b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.84, P_activation_interface_spacer_aft_end_b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.85, P_activation_interface_spacer_aft_end_b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.86, P_activation_interface_spacer_aft_end_b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.87, P_activation_interface_spacer_aft_end_b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.88, P_activation_interface_spacer_aft_end_b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.89, P_activation_interface_spacer_aft_end_b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.90, P_activation_interface_spacer_aft_end_b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.91, P_activation_interface_spacer_aft_end_b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.92, P_activation_interface_spacer_aft_end_b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.93, P_activation_interface_spacer_aft_end_b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.94, P_activation_interface_spacer_aft_end_b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.95, P_activation_interface_spacer_aft_end_b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.96, P_activation_interface_spacer_aft_end_b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.97, P_activation_interface_spacer_aft_end_b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.98, R_ACTIVATE_FB2.2, R_ACTIVATE_FREQ.2, U_ACTIVATE_BOOST.6, U_ACTIVATE_BOOST.7, U_ACTIVATE_BOOST.11, U_ACTIVATE_BOOST.12, U_ACTIVATE_BOOST.13, U_ACTIVATE_BOOST.14, U_ACTIVATE_BOOST.15, U_HACC.5, U_HACC.7, U_HACC.10, U_HACC.12, U_HACC.13, U_HACC.16
GPIO_EXT_0: J_activation_interface_spacer_activatio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.31, P_activation_interface_spacer_aft_end_b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.32
GPIO_EXT_1: J_activation_interface_spacer_activatio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.32, P_activation_interface_spacer_aft_end_b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.33
GPIO_EXT_2: J_activation_interface_spacer_activatio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.33, P_activation_interface_spacer_aft_end_b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.34
GPIO_EXT_3: J_activation_interface_spacer_activatio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.34, P_activation_interface_spacer_aft_end_b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.35
H3LIS_INT1: J_activation_interface_spacer_activatio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.35, U_HACC.11
I2C3_SCL: J_activation_interface_spacer_activatio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.36, U_HACC.4
I2C3_SDA: J_activation_interface_spacer_activatio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.37, U_HACC.6
JUMP_WAKE: J_activation_interface_spacer_activatio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.38, P_activation_interface_spacer_aft_end_b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.36
NRST: J_activation_interface_spacer_activatio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.39, P_activation_interface_spacer_aft_end_b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.37
SWO: J_activation_interface_spacer_activatio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.40, P_activation_interface_spacer_aft_end_b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.38
SYS_I2C_SCL: J_activation_interface_spacer_activatio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.41, P_activation_interface_spacer_aft_end_b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.39
SYS_I2C_SDA: J_activation_interface_spacer_activatio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.42, P_activation_interface_spacer_aft_end_b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.40
SYS_SPI_CS_FIN: J_activation_interface_spacer_activatio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.43, P_activation_interface_spacer_aft_end_b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.41
SYS_SPI_MISO: J_activation_interface_spacer_activatio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.44, P_activation_interface_spacer_aft_end_b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.42
SYS_SPI_MOSI: J_activation_interface_spacer_activatio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.45, P_activation_interface_spacer_aft_end_b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.43
SYS_SPI_SCLK: J_activation_interface_spacer_activatio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.46, P_activation_interface_spacer_aft_end_b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.44
